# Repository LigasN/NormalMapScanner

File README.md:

# NormalMapScanner
Experimental stand for generating normal maps for quasi-flat objects.

## Description
A fully automatic system that generates normal maps for nearly flat objects. The process of generation consists in taking pictures with spotlighting from different sides and computation of normals. The repository consists of all projects (hardware and software) that combined result in a working stand.

## Discussions
I would like to kindly invite you to check the [discussions page](https://github.com/LigasN/NormalMapScanner/discussions).

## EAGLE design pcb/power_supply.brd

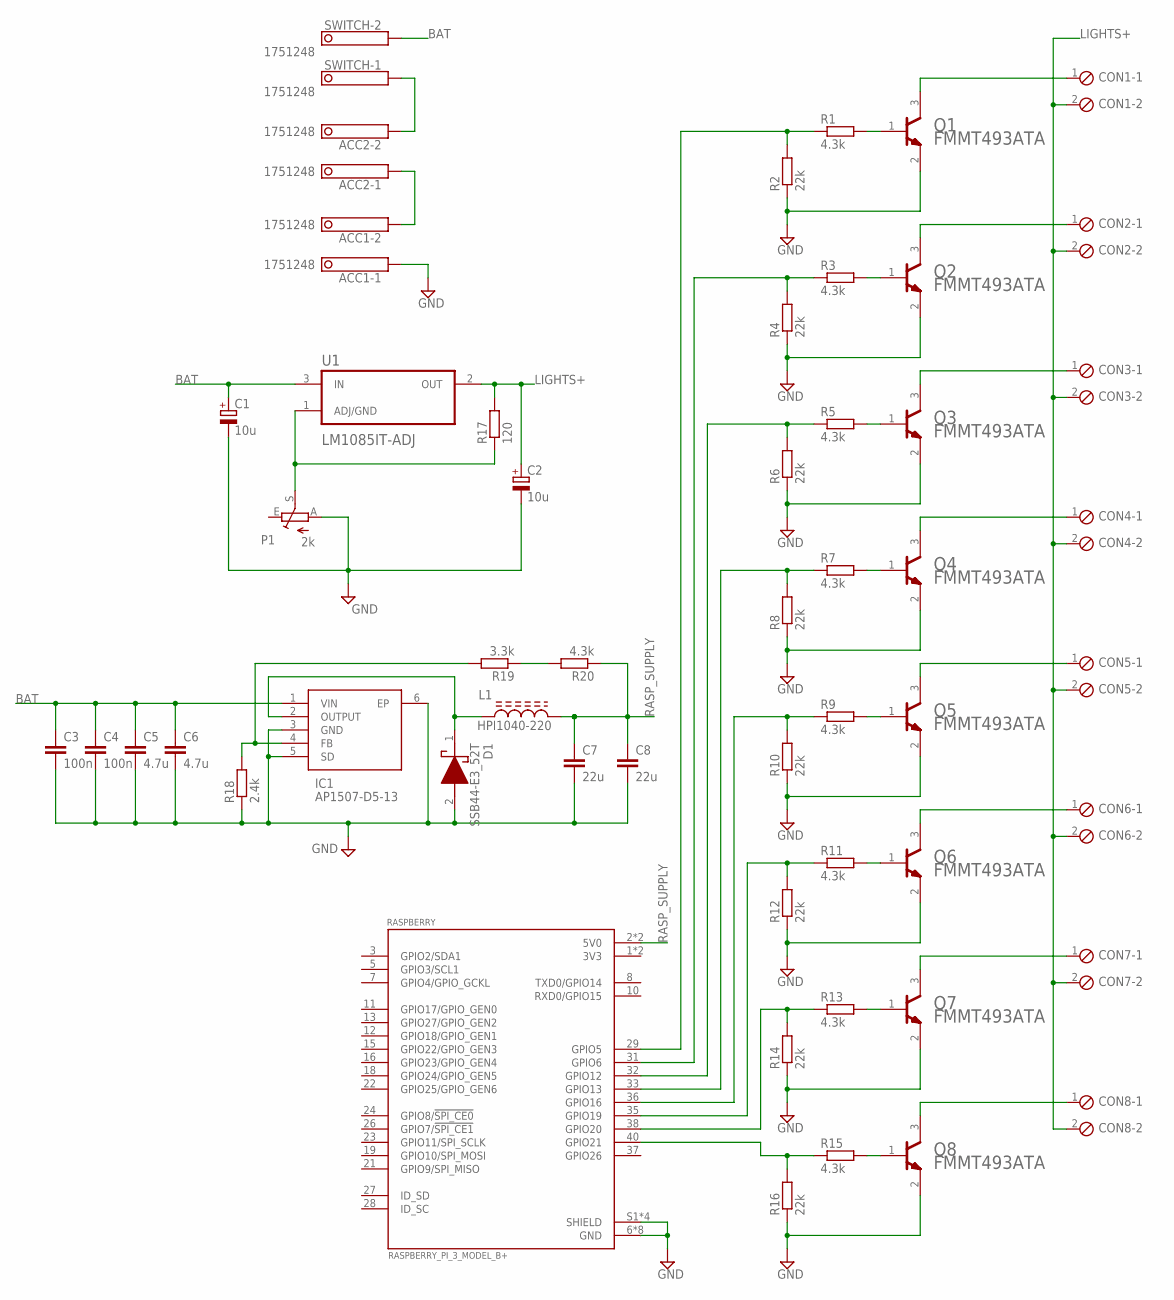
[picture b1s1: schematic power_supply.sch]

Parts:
ACC1, ACC2: 1751248
C1, C2: 10u; B/3528-21R
C3, C4: 100n; C0603
C5, C6: 4.7u; C1206
C7, C8: 22u; C1206
CON1, CON2, CON3, CON4, CON5, CON6, CON7, CON8: +; 2POL254
D1: SSB44-E3_52T; DIOM5436X244N
IC1: AP1507-D5-13; AP1507D513
L1: HPI1040-220; INDM102100X510N
P1: 2k; CA6V
Q1, Q2, Q3, Q4, Q5, Q6, Q7, Q8: DIODES_FMMT493ATADIODES_FMMT493ATA_0_0; DIODES_FMMT493ATA_0
R1, R3, R5, R7, R9, R11, R13, R15, R20: 4.3k; R0805
R2, R4, R6, R8, R10, R12, R14, R16: 22k; R0805
R17: 120; R0805
R18: 2.4k; R0805
R19: 3.3k; R0805
RASPBERRY: RASPBERRY_PI_3_MODEL_B+; MODULE_RASPBERRY_PI_3_MODEL_B+
SWITCH: 1751248
U1: LM1085IT-ADJ; TO254P1054X470X1955-3

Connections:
3V3: RASPBERRY.1 (3V3), RASPBERRY.17 (3V3)
BAT: C1.+, C3.1, C4.1, C5.1, C6.1, IC1.1 (VIN), SWITCH.2, U1.3 (IN)
GND: ACC1.1, C1.-, C2.-, C3.2, C4.2, C5.2, C6.2, C7.2, C8.2, D1.2 (A), IC1.3 (GND), IC1.5 (SD), IC1.6 (EP), P1.A, Q1.2 (E), Q2.2 (E), Q3.2 (E), Q4.2 (E), Q5.2 (E), Q6.2 (E), Q7.2 (E), Q8.2 (E), R2.1, R4.1, R6.1, R8.1, R10.1, R12.1, R14.1, R16.1, R18.1, RASPBERRY.6 (GND), RASPBERRY.9 (GND), RASPBERRY.14 (GND), RASPBERRY.20 (GND), RASPBERRY.25 (GND), RASPBERRY.30 (GND), RASPBERRY.34 (GND), RASPBERRY.39 (GND), RASPBERRY.S1 (SHIELD), RASPBERRY.S2 (SHIELD), RASPBERRY.S3 (SHIELD), RASPBERRY.S4 (SHIELD)
LIGHTS+: C2.+, CON1.2, CON2.2, CON3.2, CON4.2, CON5.2, CON6.2, CON7.2, CON8.2, R17.2, U1.2 (OUT)
unnamed: CON1.1, Q1.3 (C)
unnamed: R19.1, R20.2
unnamed: ACC1.2, ACC2.1
unnamed: IC1.4 (FB), R18.2, R19.2
unnamed: Q2.1 (B), R3.2
unnamed: CON2.1, Q2.3 (C)
unnamed: ACC2.2, SWITCH.1
unnamed: Q3.1 (B), R5.2
unnamed: CON3.1, Q3.3 (C)
unnamed: Q4.1 (B), R7.2
unnamed: CON4.1, Q4.3 (C)
unnamed: Q5.1 (B), R9.2
unnamed: CON5.1, Q5.3 (C)
unnamed: R1.1, R2.2, RASPBERRY.29 (GPIO5)
unnamed: R3.1, R4.2, RASPBERRY.31 (GPIO6)
unnamed: R5.1, R6.2, RASPBERRY.32 (GPIO12)
unnamed: Q1.1 (B), R1.2
unnamed: R7.1, R8.2, RASPBERRY.33 (GPIO13)
unnamed: R9.1, R10.2, RASPBERRY.36 (GPIO16)
unnamed: R11.1, R12.2, RASPBERRY.35 (GPIO19)
unnamed: R13.1, R14.2, RASPBERRY.38 (GPIO20)
unnamed: R15.1, R16.2, RASPBERRY.40 (GPIO21)
unnamed: P1.S, R17.1, U1.1 (ADJ/GND)
unnamed: D1.1 (K), IC1.2 (OUTPUT), L1.1
unnamed: Q6.1 (B), R11.2
unnamed: CON6.1, Q6.3 (C)
unnamed: Q7.1 (B), R13.2
unnamed: CON7.1, Q7.3 (C)
unnamed: Q8.1 (B), R15.2
unnamed: CON8.1, Q8.3 (C)
RASP_SUPPLY: C7.1, C8.1, L1.2, R20.1, RASPBERRY.2 (5V0), RASPBERRY.4 (5V0)

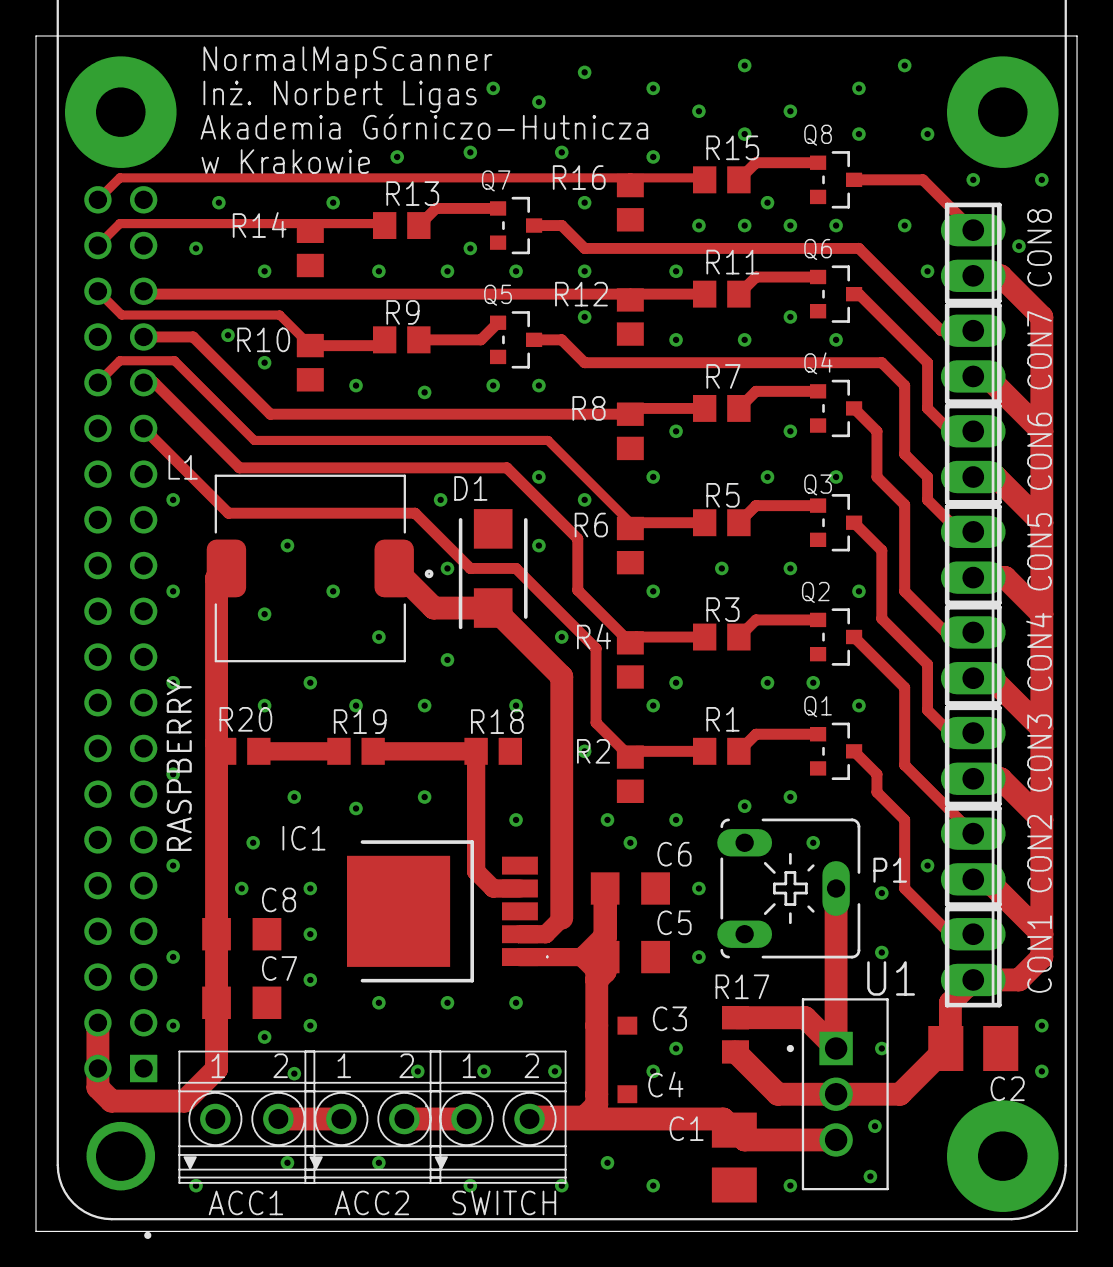
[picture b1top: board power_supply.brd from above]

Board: 2 copper layers, 57.8 x 66.4 mm, 53 parts (0 on the bottom side), 35 nets.

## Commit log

2021-10-28 gitignore update
2021-10-28 First documentation
2021-10-29 Update LICENSE
2021-11-21 Trying to get experimental 3D model in blender
2021-11-21 blob as figure 2
2021-11-21 cuboid sculpture done
2022-01-06 camera properties as the real one
2022-01-06 some repo cleaning
2022-01-07 light source model
2022-01-07 Light rotation
2022-01-08 NormalMap material
2022-01-08 all light sources, and input images v.1
2022-01-14 cube
2022-01-16 python has started
2022-01-16 reading input data py
2022-01-17 gitignore tmp update
2022-01-18 Bake the normal map
2022-01-18 Update README.md
    No worklog as the discussions page is doing great
2022-01-19 beginning of the algorithm
2022-01-20 linear color space image generation
2022-01-20 trying first idea with algorithm
2022-01-22 L_vector
2022-01-22 iteration fix
2022-01-22 weights
2022-01-23 normals calculation - not working v.1
2022-01-23 coversion needed
2022-01-26 Refactor - convertion to sum of colors right after loading
2022-02-03 something - conversion to PIL, weight way to calculate normals
2022-02-04 Error in conversion to image - pillow assumes uint8 array
2022-02-05 NormalMap algorithm output in blender
2022-02-05 Patch to apply angle way to calculate normalMap
2022-02-07 tmp directory creation
2022-02-09 logging
2022-02-09 simple test images
2022-02-10 pixel position fixed
2022-02-16 Prints commented out; Equations comment improved
2022-02-16 New normal map check
2022-02-17 more debugging visualisation
2022-02-20 pinout - more or less
2022-02-21 3D printing models with signature
2022-02-23 docs assets clean up
2022-02-23 pinuot with touchscreen and SD card module
2022-02-23 typo
2022-02-23 timer pin for the display module
2022-02-23 gitignore with STM32CubeIDE and STM32CubeMX
2022-02-23 Working touch display module
2022-02-23 next try with gitignore
2022-02-23 working gitignore for STM32CubeIDE and STM32CubeMX
2022-02-24 better rounded piece in model
2022-02-24 improved model's mesh
2022-03-02 Try with waveshare lib
2022-03-04 Synchronisation error
2022-03-04 formatting
2022-03-05 GUI with informations about camera status and errors. No correct text placed yet
2022-03-05 Status and error messages on the screen
2022-03-06 Log textbox
2022-03-06 Logging with variadic, so like printf
2022-03-09 Some data padding fixed in libraries, GUI_Console added, newline sign support added
2022-03-21 Huge commit (sorry for that) - real model scanning by hand, camera initialisation (synchronisation fixed and now overrun error)
2022-03-24 Some debug GUI beautifying
2022-03-26 Known registers described, with new values (still needs more work), no error on DCMI and no information if succeed
2022-03-31 Checking values in buffer, correct buffer size dependency
2022-04-02 Working display on NUCLEO-F767ZI
2022-04-02 Clk correction for LCD
2022-04-03 Pinout and perypherial configuration for NUCLEO-F767ZI
2022-04-08 failed try
2022-04-21 cleanup after change to raspberry
2022-04-22 stand construction - barrel hinge female
2022-04-23 barrel_hinge-male and update for female part
2022-04-23 parametrized bar
2022-04-23 power supply circuit - Linear Voltage Regulator
2022-04-24 pipe and corrected bar length
2022-04-24 barrel hinge
2022-04-24 blender-python scripts to test light source height dependency on the output normal map
2022-04-24 Start of the implementation - possibility to provide arguments to python script calculating normal map texture
2022-04-24 quick fix, missing libraries
2022-04-25 angle calculation after light height change fix
2022-04-26 adjustable leg with hinge attached
2022-04-27 leg with bolts
2022-04-27 angle iron
2022-04-27 all parts seems ready
2022-04-30 fix of flat bar length, connection of some parts in stand
2022-05-01 legs connected
2022-05-01 legs grounded
2022-05-01 stand connected, box for pcb boards
2022-05-02 pcb - connectors, raspberry
2022-05-02 stand construction - making part list v.1
2022-05-02 stand construction - trying with md
2022-05-03 stand construction - some refactoring in directory tree and summary in pdf
2022-05-08 needless image
2022-05-08 pcb - voltage regulators
2022-05-10 pcb - lights switching, battery replacement to 2*6V
2022-05-11 Some battery replacement and stuff
2022-05-15 pcb - schematic done for now
2022-05-16 pcb - a little bit closer simulation
2022-05-23 pcb - board
2022-05-28 stand_construction - holders
2022-05-28 pcb - not turning off leds fix
2022-06-02 raspberry - tools to test camera and GPIO
2022-06-03 tools - light toggling analiser in progres
2022-06-04 light toggling tool - hist and preview ready
2022-06-17 tools - stuff
2022-06-19 pcb - new raspberry supply
2022-06-25 pcb - schemat updated
2022-06-25 pcb - updated simulation
2022-06-26 pcb - board partially updated
2022-06-27 pcb - elements placed in the right places
2022-06-27 pcb - routes placed
2022-06-27 pcb - better supply route
2022-06-27 pcb - 5V pins connected
2022-06-27 pcb - ERC, DRC
2022-06-27 pcb - GND top layer
2022-06-27 pcb - vias placed
2022-06-28 pcb - gerber files, pcb ordered
2022-07-09 pcb - additional files
2022-07-13 board_box - camera case is placed
2022-07-14 board box - raspberry placed
2022-07-15 board box - fixed camera box position
2022-07-15 board box - battery case placement
2022-07-15 board box - switch
2022-07-15 board box - walls
2022-07-16 board box - holes
2022-07-16 board box - hdmi hole
2022-07-16 board box - leds hole
2022-07-16 board box - board box bottom is ready
2022-07-16 board box - cover
2022-07-16 board box - text
2022-07-16 board box - bar holder
2022-07-17 board box - holder fix
2022-07-17 board box - holders/connectors
2022-07-17 board box - ready
2022-07-18 board box - cables openings
2022-07-19 board box - done to be printed
2022-07-21 normalmap calculating script refactoring v.1
2022-07-23 software - calculating script refactored
2022-07-23 software - test normal map script done
2022-07-23 software - start work on app
2022-07-23 software - stand driver v.1
2022-07-26 gitignore
2022-07-26 software - script makes images, saves them on the disk and calculates normalmap
2022-07-26 software - tmp directory for the output
2022-07-28 App - first attempt to GUI
2022-07-29 App - fullscreen
2022-07-31 stand - box on stand partially, correction of the arm parts length
2022-07-31 App - GUI screens
2022-08-02 App - Main menu
2022-08-03 App - gather gui part.1
2022-08-04 App - try to implement camera preview
2022-08-04 App - correct GPIO ids
2022-08-04 App - try to get image from camera
2022-08-04 App - fixed problem with image reloading
2022-08-04 App - checking camera works
2022-08-04 App - stand intro
2022-08-04 App - normal map generation
2022-08-05 App - calculating normal map menu
2022-08-05 App - fixed choosing path in calculation menu
2022-08-06 App - workspace path
2022-08-07 App - run script
2022-08-07 App - fixes in linux
2022-08-08 App - progressbar
2022-08-08 App - progress bar in sync
2022-08-08 App - check image fix
2022-08-09 App - refresh normalmap
2022-08-09 App - normal map preview
2022-08-09 experiments and tests
2022-08-10 App - gathering preview
2022-08-10 App - universal preview icon
2022-08-10 App - no show after normal map generation
2022-08-10 App - normalmap in app preview
2022-08-11 App - try to get normalmap preview
2022-08-11 App - workspace refresh in calculation menu
2022-08-11 App - refreshing fix
2022-09-02 battery_life_test
2022-09-02 battery life test
2022-09-04 max size test outside
2022-09-08 measurements
2022-09-08 refactor
2022-09-29 settings for minimal stand size
2022-09-29 App - main menu removed unused options/buttons
2022-09-29 App - resolution settings
2022-09-29 App - resolution set option works
2022-09-29 App - fix bug caused by refactor
2022-09-29 App -more logging
2022-09-29 App - AsyncImage and refactor
2022-09-29 App - progress bar for all calculations, not only wektors
2022-09-29 multithreading - first try to move out vector calculations
2022-09-30 delay change in stand driver
2022-10-26 stl - bar holder diameter fix
